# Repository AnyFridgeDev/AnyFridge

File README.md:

# AnyFridge

## GitHub
[GitHub](https://github.com/AnyFridgeDev/AnyFridge)

## Authors
- [Isaac Fletcher](https://github.com/isaac-fletcher)
- [Ethan Anderson](https://github.com/Elan456)
- [Caden Allen](https://github.com/coolguycaden)

## Project Overview

This is the development repository for AnyFridge, a compact device that brings smart features to any refrigerator. No need to buy the latest expensive model!
It is a WiFi-connected UPC barcode scanner that mounts magnetically to your fridge to make keeping track of your store purchases extremely convenient. Each item you scan will be cataloged in a web app that lets you view and manage your inventory levels.

## Organization

This repository is organized into the following sections:
    
    hardware/ - Stores system schematics and PCB for custom system hardware
        
        libraries/ - Stores custom libraries containing custom components in the schematics
    
    software/ - Contains custom firmware written for the ESP32
        
    webapp/ - Contains Python web app to handle inventory tracking management
    
    docs/ - Stores documentation about the project hardware and software

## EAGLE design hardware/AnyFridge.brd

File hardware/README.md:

## AnyFridge Hardware Schematics

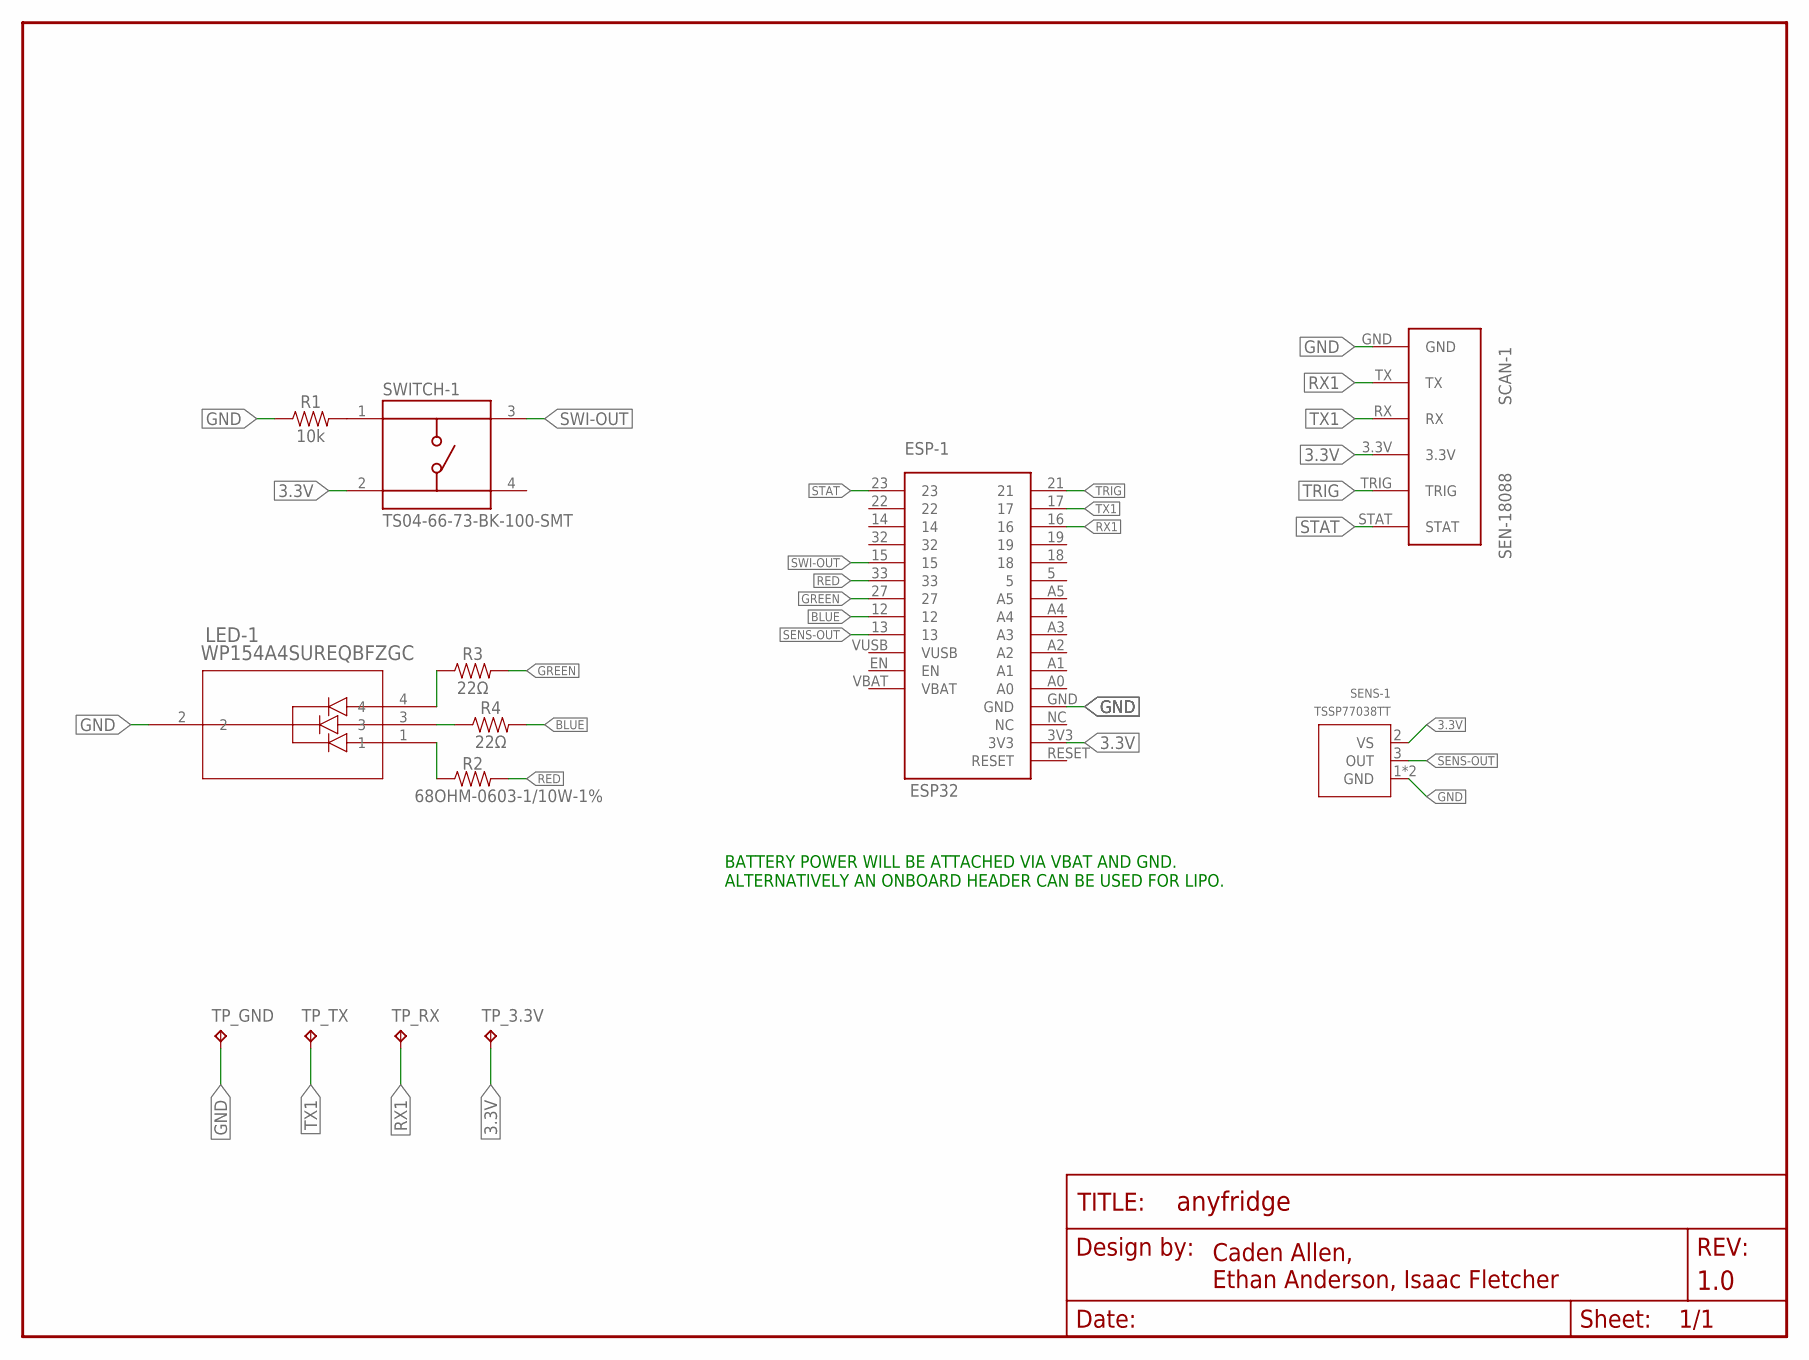
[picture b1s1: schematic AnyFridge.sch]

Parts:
ESP-1: ESP32
FRAME1: FRAME-LETTERNO_PACKAGE; DUMMY
LED-1: WP154A4SUREQBFZGC; LED4_WP154A4SUREQBFZGC_KNB
R1: 10k; AXIAL-0.3
R2: 68OHM-0603-1/10W-1%; 0603
R3, R4: 22Ω; 0603
SCAN-1: SEN-18088
SENS-1: TSSP77038TT
SWITCH-1: TS04-66-73-BK-100-SMT; SW_TS04-66-73-BK-100-SMT
TP_3.3V: TPPAD1-13; P1-13
TP_GND: TPPAD1-13; P1-13
TP_RX: TPPAD1-13; P1-13
TP_TX: TPPAD1-13; P1-13

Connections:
3.3V: ESP-1.3V3, SCAN-1.3.3V, SENS-1.2 (VS), SWITCH-1.2, TP_3.3V.TP
BLUE: ESP-1.12, R4.2
BLUE-IN: LED-1.3, R4.1
GND: ESP-1.GND, LED-1.2, R1.P$1 (1), SCAN-1.GND, SENS-1.1 (GND), SENS-1.4 (GND), TP_GND.TP
GREEN: ESP-1.27, R3.2
GREEN-IN: LED-1.4, R3.1
unnamed: R1.P$2 (2), SWITCH-1.1
RED: ESP-1.33, R2.2
RED-IN: LED-1.1, R2.1
RX1: ESP-1.16, SCAN-1.TX, TP_RX.TP
SENS-OUT: ESP-1.13, SENS-1.3 (OUT)
STAT: ESP-1.23, SCAN-1.STAT
SWI-OUT: ESP-1.15, SWITCH-1.3
TRIG: ESP-1.21, SCAN-1.TRIG
TX1: ESP-1.17, SCAN-1.RX, TP_TX.TP

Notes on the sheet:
BATTERY POWER WILL BE ATTACHED VIA VBAT AND GND. ALTERNATIVELY AN ONBOARD HEADER CAN BE USED FOR LIPO.

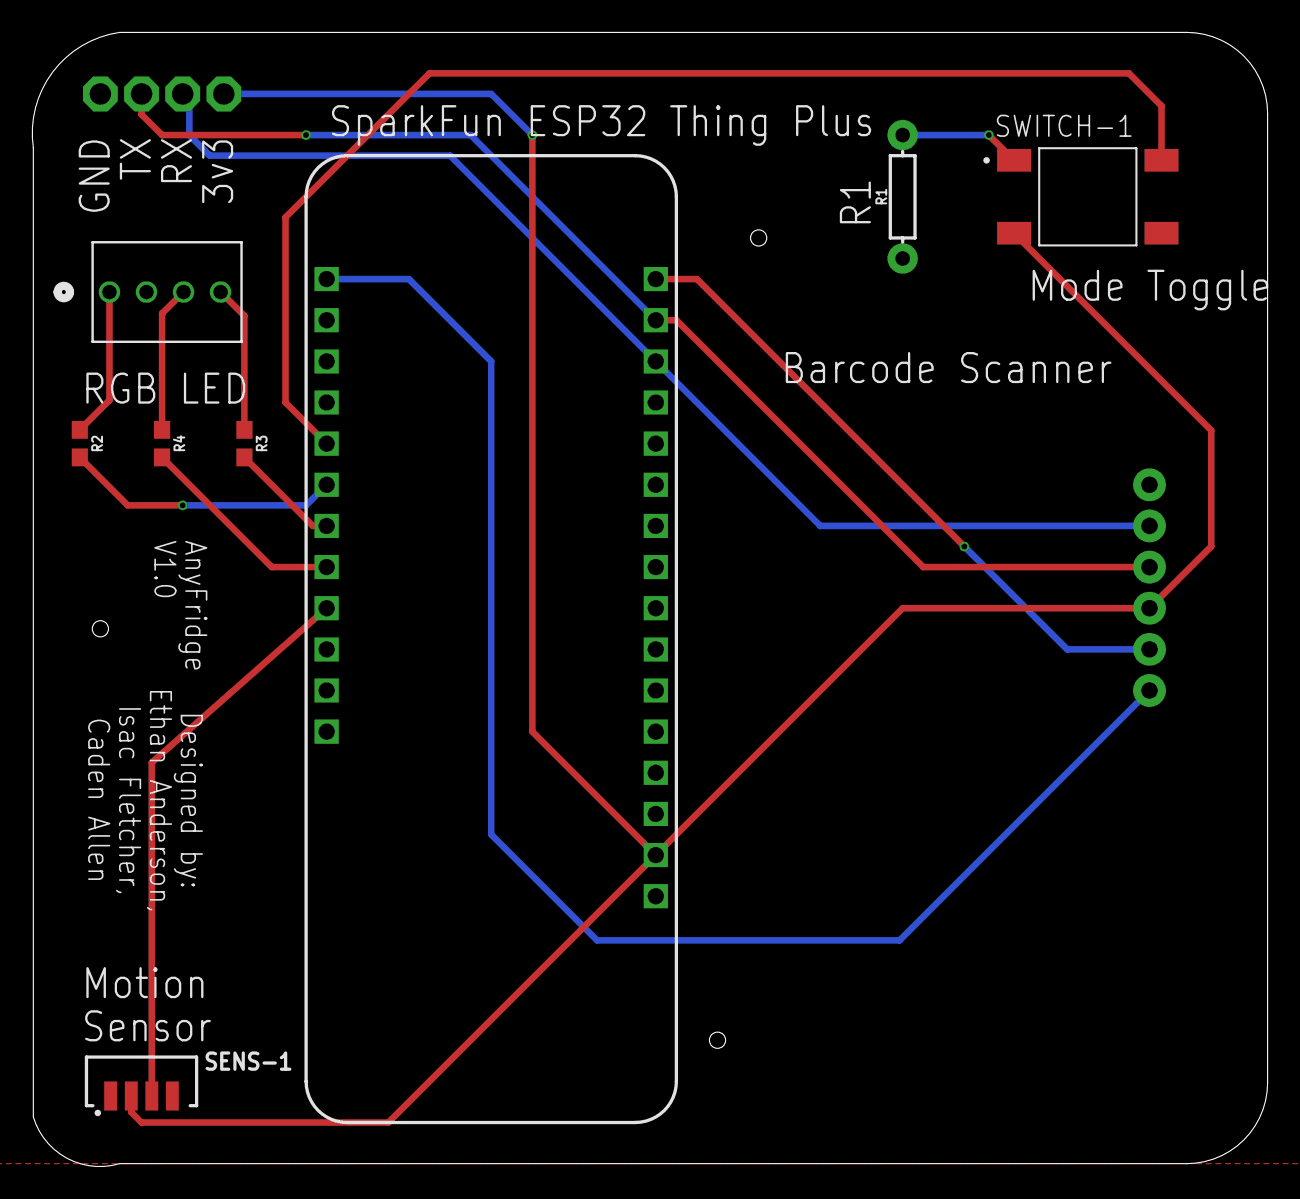
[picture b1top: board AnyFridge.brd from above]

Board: 2 copper layers, 76.3 x 70.0 mm, 14 parts (1 on the bottom side), 15 nets.

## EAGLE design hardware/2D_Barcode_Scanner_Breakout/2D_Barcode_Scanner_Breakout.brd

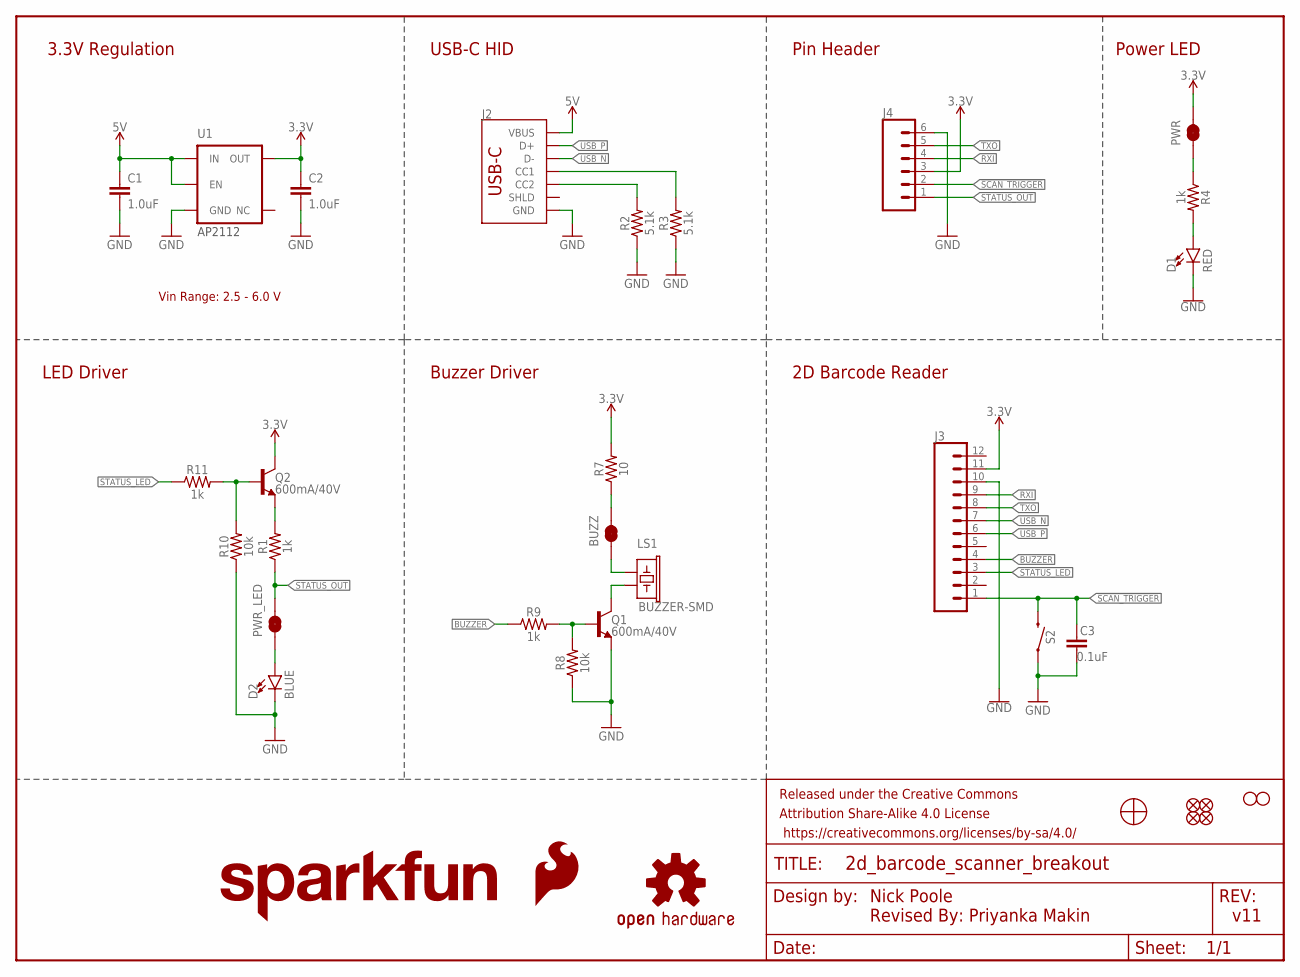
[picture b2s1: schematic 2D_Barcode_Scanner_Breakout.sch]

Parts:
BUZZ: JUMPER-SMT_2_NC_TRACE_SILK; SMT-JUMPER_2_NC_TRACE_SILK
C1, C2: 1.0uF; 0603
C3: 0.1uF; 0603
D1: RED; LED-0603
D2: BLUE; LED-0603
FD1, FD2, FD3, FD4: FIDUCIALUFIDUCIAL; FIDUCIAL-MICRO
FRAME1: FRAME-LETTER; CREATIVE_COMMONS
H2, H3: STAND-OFF
J2: USB_C_2-LAYER_PADS; USB-C-16P-2LAYER-PADS
J3: CONN_12FPC_12_0.5MM; FPC_12_0.5MM
J4: CONN_06NO_SILK_FEMALE_PTH; 1X06_NO_SILK
LOGO1: OSHW-LOGOS; OSHW-LOGO-S
LOGO2: SFE_LOGO_FLAME.1_INCH; SFE_LOGO_FLAME_.1
LOGO3: SFE_LOGO_NAME.1_INCH; SFE_LOGO_NAME_.1
LS1: BUZZER-SMD; BUZZER-CCV
PWR: JUMPER-SMT_2_NC_TRACE_SILK; SMT-JUMPER_2_NC_TRACE_SILK
PWR_LED: JUMPER-SMT_2_NC_TRACE_SILK; SMT-JUMPER_2_NC_TRACE_SILK
Q1, Q2: 600mA/40V; SOT23-3
R1, R4, R9, R11: 1k; 0603
R2, R3: 5.1k; 0603
R7: 10; 0603
R8, R10: 10k; 0603
S2: MOMENTARY-SWITCH-SPST-SMD-5.2MM-TALL; TACTILE_SWITCH_SMD_5.2MM
U1: 3.3V; SOT23-5
U2: BARCODE_SCANNER_MOUNT

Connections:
3.3V: C2.1, J3.11, J4.3, PWR.2, Q2.3 (C), R7.2, U1.5 (OUT)
5V: C1.1, J2.VBUS1 (VBUS), J2.VBUS2 (VBUS), U1.1 (IN), U1.3 (EN)
!SCAN_TRIGGER!: C3.1, J3.1, J4.2, S2.3 (2)
BUZZER: J3.4, R9.1
CC3: J2.A5 (CC1), R3.2
CC4: J2.B5 (CC2), R2.2
GND: C1.2, C2.2, C3.2, D1.C, D2.C, J2.GND, J2.GND2 (GND), J3.10, J4.6, Q1.2 (E), R2.1, R3.1, R8.1, R10.1, S2.1, U1.2 (GND)
unnamed: BUZZ.2, R7.1
unnamed: LS1.- (2), Q1.3 (C)
unnamed: BUZZ.1, LS1.+ (1)
unnamed: Q2.2 (E), R1.2
unnamed: Q1.1 (B), R8.2, R9.2
unnamed: PWR.1, R4.1
unnamed: Q2.1 (B), R10.2, R11.2
unnamed: D2.A, PWR_LED.1
unnamed: D1.A, R4.2
RXI: J3.9, J4.4
STATUS_LED: J3.3, R11.1
STATUS_OUT: J4.1, PWR_LED.2, R1.1
TXO: J3.8, J4.5
USB_N: J2.A7 (D-), J2.B7 (D-), J3.7
USB_P: J2.A6 (D+), J2.B6 (D+), J3.6

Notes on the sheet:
3.3V Regulation
AP2112
Pin Header
2D Barcode Reader
LED Driver
Buzzer Driver
USB-C HID
Power LED
Nick Poole Revised By: Priyanka Makin
v11
Vin Range: 2.5 - 6.0 V

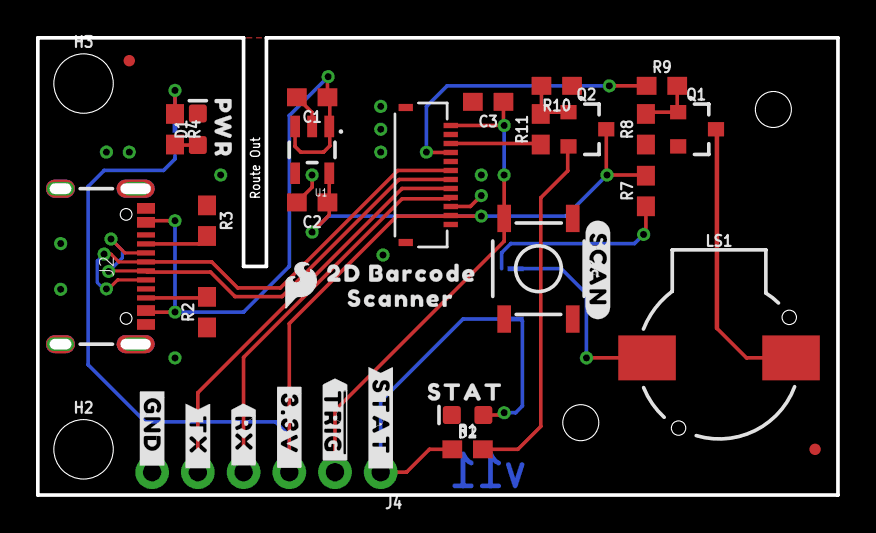
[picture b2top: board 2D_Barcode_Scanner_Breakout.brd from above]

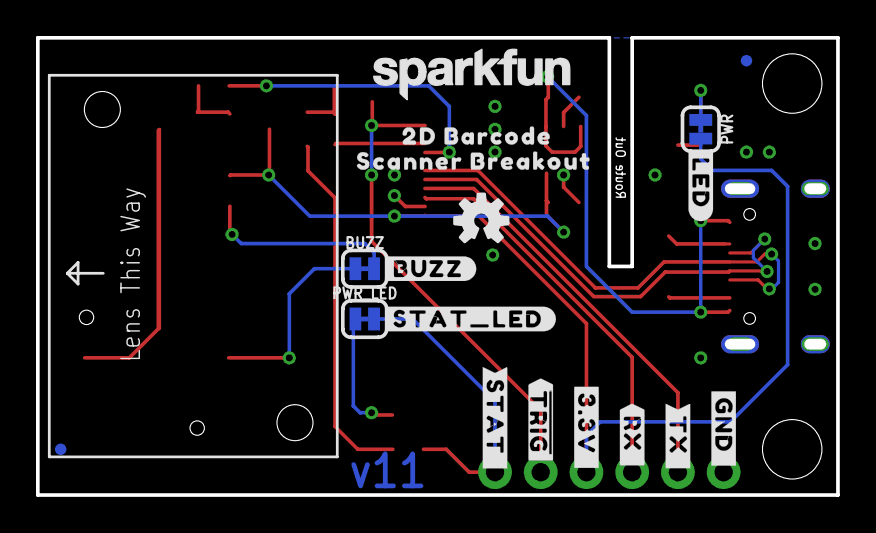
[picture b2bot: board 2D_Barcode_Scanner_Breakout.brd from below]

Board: 2 copper layers, 44.1 x 25.0 mm, 58 parts (19 on the bottom side), 22 nets.

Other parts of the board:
U$1, U$7: ##TRIG##0
U$2, U$21: #STAT_#0
U$3: STAT0
U$4: #SCAN#0
U$5: #BUZZ#0
U$6: #STAT_LED#0
U$8: PWR0
U$9: #LED#0
U$17, U$18: 2D_BARCODE0
U$19: SCANNER0
U$20: SCANNER_BREAKOUT0
U$26, U$27: #TX_#0
U$28, U$29: #3#3V_#0
U$30, U$31: #RX_#0
U$32, U$33: #GND_#0

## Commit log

2025-02-13 Add README files
2025-02-13 Added schematic files
2025-02-13 hehe haha made sensor
2025-02-16 Added frame
2025-02-16 Added ESP32 and custom frame libraries. Updated main schematic.
2025-02-19 Add barcode (SEN-18088) library
2025-02-19 Adjust hole positions and diameter on footprint based on sparkfun eagle files
2025-02-20 added misc parts library
2025-02-20 most of schematic finished
2025-02-20 Wire LED + Button, change UART
2025-02-20 Project overview rewording
2025-02-20 Updated schematic
2025-02-20 Added schematic grouping
2025-02-23 Updated ESP32 library to be accurately scaled
2025-02-24 updated board
2025-02-24 Rotated barcode scanner
2025-02-25 Removed ugly dimensions from barcode scanner
2025-02-25 Add GND copper pour on top layer
2025-02-26 Added comment to schematic
2025-02-26 Increase traces to 16mm and add test points for UART
2025-02-26 Make PCB much smaller
2025-02-26 Add initial silkscreen
2025-02-26 attempted fix for LED spacing
2025-02-26 Updated board and schematic to use appropriate ESP library
2025-02-26 Cleaned repository and updated .gitignore
2025-02-27 Make traces to LED less wonky
2025-02-27 Align all traces to 45deg angles
2025-02-27 Removed sensor file
2025-02-27 Rounded corner
2025-02-27 Minor updates.
2025-02-27 Added 120 ohm resistor to board/schematic
2025-02-27 schematic updated
2025-02-27 Add oshpark rules
2025-02-27 Add Green and Blue resistors
2025-02-27 Put project name + revision in silkscreen, rename resistor to LED pins
2025-03-06 Add initial platformio project
2025-03-10 Fix TX + RX on Scanner LIB + Flip Scanner on AnyFridgeBRD
2025-03-11 started on sleeve design
2025-03-11 Add barcode test
2025-03-11 Add wifi test
2025-03-11 Ignore my deliverables folder
2025-03-13 Initial webapp ui and request handler + unit tests
2025-03-13 Add mounting holes
2025-03-13 move resistors to top layer
2025-03-13 Silkscreen fixes
2025-03-13 Fix more silkscreen problems
2025-03-17 Updated Gradio to listen on *
2025-03-17 Added core functionality and additional tests.
2025-03-17 Updated to support add and delete
2025-03-17 Updated code
2025-03-18 prototype ui created
2025-03-18 new changes to item html design
2025-03-18 login page, user_id prompt, and experimental item population. needs more work
2025-03-22 Add initial testing.txt
2025-03-22 Rename ui.py to gradio.py and rename test_server to test_request_handling
2025-03-22 Cleanup wifi test a bit
2025-03-24 almost full functionality, only missing delete button usage
2025-03-25 better file naming for testing
2025-03-25 Testing.txt add partner names
2025-03-25 Updated to create user json if it doesn't exist.
2025-03-25 Updated to include sample integration testing.
2025-03-25 Remove autostart of request_handler, change endpoint to api/update for request handler
2025-03-25 add create_user method
2025-03-25 Add .strip when upc code ingesting
2025-03-25 Updated to support https
2025-03-25 Updated integration test
2025-03-25 Add local curl frotnend update test
2025-03-25 Testing.txt reformating and clarifications
2025-03-25 Updated integration test again
2025-03-25 testing.txt update
2025-03-25 Add EC2 startup script
2025-03-25 experimental changes for delete button functionality
2025-04-08 Add test button and test blink
2025-04-17 Fix button to INPUT_PULLDOWN
2025-04-17 Barcode logic changes
2025-04-17 working delete button + nutrition information. Attempting to add fancy expiration date logic
2025-04-18 updated sleeve
2025-04-19 Updated source to include NetWizard and fix barcode scanning issues
2025-04-24 Add better request handler logs
2025-04-24 Updated source to sense motion instead of scan continuously
2025-04-24 preferences user id saving
2025-04-26 fully working expiration date + auto-refresh
2025-04-30 Minor bug fixes
2025-04-30 experimental autorefresh items + additional changes

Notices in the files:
parts and their libraries:
SparkFun-Capacitors: Licensing: Creative Commons ShareAlike 4.0 International - https://creativecommons.org/licenses/by-sa/4.0
SparkFun-Aesthetics: Released under the Creative Commons Attribution Share-Alike 4.0 License
SparkFun-Aesthetics: https://creativecommons.org/licenses/by-sa/4.0
